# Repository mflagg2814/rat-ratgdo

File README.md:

# XIAO ESP32-C6 / ESP32-C5 board

> [!IMPORTANT]
> This board has been built and tested to work with ESP32-C6.\
> Use it at your own risk and without expectation of support.\

AI disclosure: Board layout is my own. AI was used for verification, documentation, schematic cleanup, and minor board cleanup.

[`kicad_files/XIAO ESP32C6`](kicad_files/XIAO%20ESP32C6) is a small Security+ 2.0 interface for the ESPHome `secplus_gdo` component, built around a surface-mounted Seeed XIAO ESP32-C6. Compared with the [D1 Mini - ESP32](kicad_files/D1%20Mini%20-%20ESP32) board it is based on:

- **MCU:** a XIAO ESP32-C6 replaces the D1 Mini ESP32. TX is on GPIO22 (D4) and RX on GPIO18 (D10). As before, the module is powered from its own USB port. The same footprint and pinout also accept a Seeed XIAO ESP32-C5 (see the [board README](kicad_files/XIAO%20ESP32C6/README.md#xiao-esp32-c5-compatibility) for the C5 substitutions).
- **RX:** a 10k pull-up to 3V3 is added, because the firmware does not enable an internal one.
- **Values:** the TX GPIO pulldown is 4.7k (was 10k), and the RED-to-ground bias is 100k (was 10k).
- **Protection:** a 15 V unidirectional TVS is added on the RED line.
- **Obstruction:** the black-wire sensing circuit is removed, since obstruction status is read from the serial protocol.
- **Terminal:** A single 2-pole WAGO push-button terminal replaces the 3-pole connector options. Accepts 20-24 AWG.

The folder includes a [BOM](kicad_files/XIAO%20ESP32C6/BOM.md) with DigiKey part numbers, a [schematic PDF](kicad_files/XIAO%20ESP32C6/c6gdo-schematic.pdf), and a [README](kicad_files/XIAO%20ESP32C6/README.md) with the full list of changes and the reasoning behind them. The project needs KiCad 10 and contains its own symbol, footprint and 3D-model libraries.

## XIAO ESP32-C5 compatibility
This board was designed for the XIAO ESP32-C6. The pinouts are also chosen for XIAO ESP32-C5 compatibility. I'm unsure of precedent for the GDO firmware- it may or may not function on C5.

## Firmware
Intended for use with SecPlus GDO firmware using the ESP-IDF framework.

An example ESPHome YAML would be an adaptation of `grgdov3-board-secplus-gdo-thread.yaml`, found [here](https://github.com/GelidusResearch/grgdo). Note that you will at a minimum need to remap the UART pins and change the board/variant to match.

## Case
STLs for a compact 3D printed case will be available upon validation against the final build. There will be an internal antenna variant plus C6 and C5 external antenna cutout variants.

---

# rat-ratgdo
RAGE
AGAINST
THE
RATGDO

Credit and inspiration for this work goes to [@rlowens](https://github.com/rlowens) to let me know that there are other technical folks out there who needed this other than myself.

## Overview
This is an open source schematic for the ratgdo, based on the v2.5 [ratgdo](https://github.com/PaulWieland/ratgdo) PCB and code but installed using the [ESPHome fork](ESPHome%20vs%20native%20ratgdo.md) of ratgdo.  This project was created to allow people who need a ratgdo solution for their garage door opener but either cannot, or choose not to, source the solution from Paul Wieland. It also ensures that the PCB can be recreated as and when the project maintainer gives up on the project (much like Chamberlain themselves might do with their MyQ Cloud Service) and stops selling PCBs. 

### You are expected to know how to create the described circuit using your own prototyping skills.  That is, this project is for people who can solder well and know how to read schematics

The ***basic*** PCB schematic shown here in the Readme does not describe any circuitry other than the serial line garage door control and obstruction sensor.  All other optional features provided by ratgdo can be reverse engineered as needed, or may already be solved by one of the schematics the community has uploaded!

 As of January 2023, there are now multiple sources for commercially sold ratgdo boards.  **However if you want to buy a pre-made ratgdo setup, we recommend purchasing one [from Paul Wieland](https://github.com/PaulWieland/ratgdo) so as to reward the original creator.**

_Simple basic schematic for a Wemos D1 Mini based module_

See images of a [working breadboard prototype](images/Breadboard_working.png) and the [subsequent soldered prototype using a D1 shield](images/Simple%20prototype%20using%20D1%20shield.jpg).  Both of these prototypes are using 2n7000 MOSFETs exclusively, but that is because they are prototypes and whether a 2n7000 will work for TX will depend greatly on who manufactured your 2n7000.  See the section below on needed components for context.

## Components needed for basic functionality
The basic schematic shown above assumes the use of through-hole components.  If you wish to use SMD components, please refer to the [FAQ](FAQ.md#what-if-i-want-to-use-sot-23-smd-components), and you can also check out the community-provided schematics, which include SMD-based designs.

For this basic design, aside from the obvious requirement of a [supported ESP-32 or ESP8266 board](Supported%20Boards.md) flashed with the [ESPHome version](https://github.com/ratgdo/esphome-ratgdo), you will need:
- 3x 10 kohm (kilo-ohm) resistors
- 1x 2n7000 MOSFET for the RX pin
- 1x AO3400A (soldered to a SOT23 to DIP adapter board) for the TX pin.

It is also recommended you aquire a suitable 3-post screw terminal and some red, white, and black wire for connecting to the door opener.  These connections are very low current, so you can get away with fairly thin wire.

**Note:**  You may **try** to use a 2n7000 MOSFETs for **both** RX and TX, however depending on the manufacturere of your 2n7000 and its production batch, it might not be 100% reliable for the TX circuit because the ~3v switching signal from the ESP8266 may not be enough to trigger the gate of the 2n7000.  There are many examples working using the 2n7000 however, so it might work.  If you have reliability issues for sending commands, we can only recommend you use the AO3400A SMD MOSFET, soldered to a SOT23-to-DIP adapter board.  

## INSTALL REQUIREMENTS
For both this basic schematic shown here in the Readme and how they it is laid out, you must use the ESPHome fork of ratgdo and - for ESP8266 based boards - select the "ratgdo v2.5x" image on the ESPhome [web installer page](https://ratgdo.github.io/esphome-ratgdo/).  For ESP32 based boards the above does not currently apply and you must use the v2.0 installer and follow our basic ESP-32 schematic we provide in the Supported Boards page.

For the ESP8266 based boards, if installing using Paul Wieland's native ratgdo installer and you install for a v2.0 board, you must wire your TX to D4 (GPIO2) rather than D1 (GPIO5).

## Having a PCB printed
You may use the files from the [schematics folder](kicad_files) to have your own PCB printed.  Shown is an example 3D render of an ESP32 based board using a Wemos ESP32 D1 board.

_An example of the D1 Mini ESP32 Wide Format_

Here is an example of a printed PCB with a raw ESP8266 and an LM2596 module, for being powered by a GDO with the battery backup capabilities.

_An example of a PCB using a bare ESP8266 and LM2596 module_

### Schematic options
The community has provided a few options of schematic files suitable for sending to a PCB printing company.
- [Wemos D1 Mini ESP8266](kicad_files/D1%20Mini%20-%20ESP8266)
- [Wemos D1 Mini ESP32](kicad_files/D1%20Mini%20-%20ESP32) (massive overkill for ratgdo but it's your choice!)
- [Wemos D1 Mini ESP32 Wide Format](kicad_files/D1%20Mini%20Wide%20-%20ESP32)
- [Bare ESP8266 module](kicad_files/Bare%20ESP8266)
- [Seeed XIAO ESP32-C6](kicad_files/XIAO%20ESP32C6) (untested; KiCad 10; see the note at the top)

> If you just want to try ordering a board from somewhere like PCBWay, then check out the most recent [build artifacts](https://github.com/Kaldek/rat-ratgdo/actions/workflows/pcb.yaml)

## How the ratgdo circuit works
The ratgdo circuitry which we cover in this project consists of two sections; Garage Door control and obstruction sensors.

### Garage Door Control
#### Description of the Chamberlain configuration
The Chamberlain garage door control circuit is a two-wire setup consisting of a Ground, and a combined +12v power and serial data line.  The serial data line is held at 12v unless data transmission is occurring.  Data transmission is performed by pulling the 12v line down to GND for each data bit.  The benefit here is that a single wire can be used for providing power to door control panels and data transmssion on a single wire.  The use of appropriately sized capacitors in door control panels means they do not switch off during data transmission.

#### How ratgdo interfaces with the Chamberlain wiring
The ratgdo taps into the red control wire and uses this single wire for transmission of commands onto the serial bus, and for receiving data from the serial bus.  As it is a single wire protocol and operates half-duplex, the ratgdo circuitry uses N-channel MOSFETs wired in a manner which allows the ESP8266 to never transmit when the serial line is already low.

In operation, this means that the ratgdo is mostly listening to the serial bus to ensure it is keeping track of the state of the door.  For example, if the door is manually opened (or opened by use of the MyQ app even), these events are broadcast onto the serial bus by the door controller.  ratgdo is therefore able to know that the state of the door has changed.  In turn, this means that when controlling ratgdo via Home Assistant, the status of the door in HA is always up to date.

#### Wiring to Garage Door

### Obstruction sensor
The ratgdo monitors the real-time state of the obstruction sensors directly.  We assume this is because obstruction status is not broadcast in real time by the door controller, and safety is paramount.  It allows you to set up real-time alerts in Home Assistant for any time the door is obstructed.  The ratgdo taps into the obstruction sensor power wire which also acts as a communication bus, however the signalling is only an ongoing status of whether the obstruction sensors are working and whether there is an obstruction.

## Contributing
This is a fully open repo, in that we welcome any and all additions for all sorts of Edge Cases.  If you come up with something and would like it to be available to the community, raise a Pull Request and we'll work with you to get it published!

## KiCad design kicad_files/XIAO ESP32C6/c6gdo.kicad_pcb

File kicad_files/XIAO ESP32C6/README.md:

# Seeed XIAO ESP32-C6 / ESP32-C5 KiCad files

> [!IMPORTANT]
> This board has been built and tested to work with ESP32-C6.\
> Use it at your own risk and without expectation of support.\
> My opener also required a patched gdolib to address a buffer overrun while opening/closing. See Firmware below.

A small (28.4 × 21.05 mm, 2-layer) Security+ 2.0 interface based on this repository's D1 Mini - ESP32 board, built around a surface-mounted [Seeed Studio XIAO ESP32-C6](https://wiki.seeedstudio.com/xiao_esp32c6_getting_started/). It connects to only the RED and WHITE wall-control wires, and the XIAO is powered from its own USB-C port.

- Schematic: [c6gdo-schematic.pdf](c6gdo-schematic.pdf) (source: `c6gdo.kicad_sch`)
- Bill of materials: [BOM.md](BOM.md) / [BOM.csv](BOM.csv)

## Case

Case STLs are in the `case` dir. Print one `bottom.stl` and one `top` per your external antenna cutout requirements. Designed for 0.2mm layer height and successfully printed in Prusament Galaxy Purple PLA.

## Firmware

The board was designed for the ESPHome [`secplus_gdo`](https://github.com/gelidusresearch/esphome-secplus-gdo) component. That component inverts the UART, which matches the two inverting MOSFET stages on this board.

Obstruction status comes from the Security+ 2.0 serial protocol, so no obstruction pin is configured.

An example ESPHome YAML would be an adaptation of `grgdov3-board-secplus-gdo-thread.yaml`, found [here](https://github.com/GelidusResearch/grgdo). Note that you will at a minimum need to remap the UART pins and change the board/variant to match.

```yaml
substitutions:
  uart_tx_pin: GPIO22 # D4
  uart_rx_pin: GPIO18 # D10

esp32:
  board: seeed_xiao_esp32c6
  flash_size: 4MB
  variant: esp32c6
  framework:
    type: esp-idf
```

### gdolib patch

My opener also required the patch in `gdolib-patch` against `GelidusResearch/gdolib` v1.2.9 (5936cab). It's provided in the event your opener behaves like mine and spams messages before gdolib can service them. I don't recommend bothering with it unless you have issues stopping your opener mid-travel or issues with opening/closing state reports. Open/close, light status, etc worked fine without the patch.

## XIAO ESP32-C5 compatibility

This board was designed for the XIAO ESP32-C6. The pinouts are also chosen for XIAO ESP32-C5 compatibility. I'm unsure of precedent for the GDO firmware- it may or may not function on C5.

If you populate a C5 instead of a C6, use this in place of the substitutions/esp32 block above:

```yaml
substitutions:
  uart_tx_pin: GPIO23 # D4
  uart_rx_pin: GPIO10 # D10

esp32:
  board: seeed_xiao_esp32c5
  flash_size: 8MB
  variant: esp32c5
  framework:
    type: esp-idf
```

## Changes from the D1 Mini - ESP32 board

The starting point is [`kicad_files/D1 Mini - ESP32`](../D1%20Mini%20-%20ESP32). The core of that design is kept as is:
- Q1 (2N7002) with a 10k series resistor into its gate for RX.
- Q2 (AO3400A) with a 1k gate resistor for TX.
- A pulldown on the TX GPIO.
- A bias resistor from RED to ground.
- No power circuitry on the board (the module is powered over its own USB).

The changes are:

| | D1 Mini - ESP32 | This board | Notes |
|-|-|-|-|
| MCU | Wemos D1 Mini ESP32: TX IO22 (D1), RX IO21 (D2) | Seeed XIAO ESP32-C6: TX GPIO22 (D4), RX GPIO18 (D10) | Smaller module with WiFi 6 / Thread. Neither pin is a C6 strapping pin, and neither conflicts with the console UART, USB-JTAG or the antenna switch. D4/D10 were chosen (instead of D3/D10) so the same board also works with a XIAO ESP32-C5 — see [XIAO ESP32-C5 compatibility](#xiao-esp32-c5-compatibility). |
| RX pull-up | None | **R5** 10k to 3V3 (new) | gdolib never enables an internal pull-up on the RX pin, so without R5 the pin floats when Q1 is off. |
| TX GPIO pulldown | 10k | **R1** 4.7k | Keeps Q2 off while the ESP32 is in reset. In reset the pin's ~45 kΩ internal pull-up is enabled, which with the old 10k pulldown would set Q2's gate to about 3.3 V × 10k / 55k ≈ 0.60 V. That is just under the AO3400A's minimum turn-on threshold of 0.65 V (0.65–1.45 V). With 4.7k the gate sits at about 0.31 V. |
| RED bias to ground | 10k | **R4** 100k | Lighter load on the opener's line: about 0.13 mA instead of 1.3 mA at 12.7 V. |
| Transient protection | None | **D1** PTVS15VS1UR 15 V, 400 W unidirectional TVS (new) | Clamps transients on the wire run to the opener. |
| Obstruction | IO23 through a 10k series resistor and 10k pulldown | Removed | Obstruction status is read from the Security+ 2.0 serial protocol. |
| Connector | Three 3-pole footprint options (5.00 mm screw terminal, 3.5 mm Phoenix MCV, 2.54 mm header) | One 2-pole WAGO 250-1402 push-button terminal | Only RED and WHITE are needed. Accepts 20-24 AWG *solid* wire. |

## Wiring and mounting

- **J1 RED** → opener's red wall-control terminal. **J1 WHITE** → opener's white terminal (ground). The labels are on the back silkscreen.
- Power the XIAO from any USB-C supply.
- Mount it with a #6-32 nylon screw through the 4.0 mm hole into a SnapSkru SPM Mini drywall anchor (see the BOM).
  - A smaller diameter screw might work better. I installed the SnapScrew, ran an included metal screw through it, then installed with the nylon screw snipped to ~1-1.5cm length. Any longer and it would bind.
  - M3.5 should also work for the mounting screw.
  - I strongly recommend against a metallic screw in this position. It may interfere with the antenna.

## PCB notes

- The XIAO sits on the top side, flush with the bottom board edge. All other parts are on the back.
- The XIAO's underside pads (24–33) are **not soldered**. The footprint has no copper for them; instead it marks each one with an F.Fab outline and a rule area, so DRC flags any via placed there. The top-layer ground fill also stays out of these areas, so a flaw in the solder mask can't short a signal or power pad to ground. These pads are also left off the schematic symbol.
- Both copper layers are ground-filled, and both fills stop at y = 55 mm, leaving the board under the XIAO's antenna end free of copper.
- Stitching vias tie the two ground fills together. Most sit on a regular 3.2 mm grid, including a row along the fill edge nearest the antenna, with a few extra vias between the parts in the center. The spacing comes from the WiFi wavelength:
  - A 2.4 GHz signal has a wavelength (λ) of about 125 mm in air, or roughly 60–70 mm in FR4.
  - A common rule of thumb keeps stitching vias no more than λ/20–λ/10 apart, about 3–6 mm. That way no patch of copper is large enough to act as a resonator or slot antenna at WiFi frequencies.
  - On this board, no point where both layers are filled is more than about 3.2 mm from a stitching via.
- Under the XIAO's two rows of edge pads, only the bottom layer is ground-filled, since the top layer holds the pads. These bottom-only strips are about 4 mm wide. Each one is joined to the rest of the bottom fill along its full length, and a column of vias runs along its inner edge. So each strip is part of the ground plane rather than a separate flap, and it is far too small to resonate at 2.4 GHz (a quarter wavelength is about 15–17 mm in FR4).

## Project layout

Everything the project uses is inside this folder. Symbols, footprints and 3D models are referenced through `${KIPRJMOD}` via the project's own `sym-lib-table` and `fp-lib-table`, so the folder can be moved or renamed and opened on another machine without extra library setup.

```
c6gdo.kicad_pro / .kicad_sch / .kicad_pcb   KiCad 10 project
c6gdo-schematic.pdf                          schematic export
BOM.md, BOM.csv                              bill of materials
gerbers/                                     Gerber + Excellon drill files
c6gdo-gerbers.zip                            the same files, zipped for upload to a PCB fab
lib/c6gdo.kicad_sym                          project symbol library
lib/c6gdo.pretty/                            project footprint library
lib/c6gdo.3dshapes/                          3D models (STEP/IGES)
images/                                      3D renders
```

The files require **KiCad 10**. The Gerbers match the current board. After any board change, re-export them: copper, mask, paste, silkscreen and Edge.Cuts layers, plus separate PTH/NPTH Excellon drill files.

Sources:
- **XIAO symbol and footprint:** derived from Seeed Studio's official XIAO KiCad library.
- **XIAO 3D model** (`lib/c6gdo.3dshapes/seeed-studio-xiao-esp32c6-v2.step`): "[3D model for Seeed Studio XIAO ESP32C6](https://www.printables.com/model/1338408-3d-model-for-seeed-studio-xiao-esp32c6)" from Printables. It is licensed under [CC BY-SA 4.0](https://creativecommons.org/licenses/by-sa/4.0/) and included unmodified.
- **WAGO footprint and 3D model:** from the [250-1402 Ultra Librarian CAD download on DigiKey](https://www.digikey.com/en/models/15551338?tab=ultralibrarian).
- **Everything else:** the remaining footprints and 3D models come from the standard KiCad libraries.

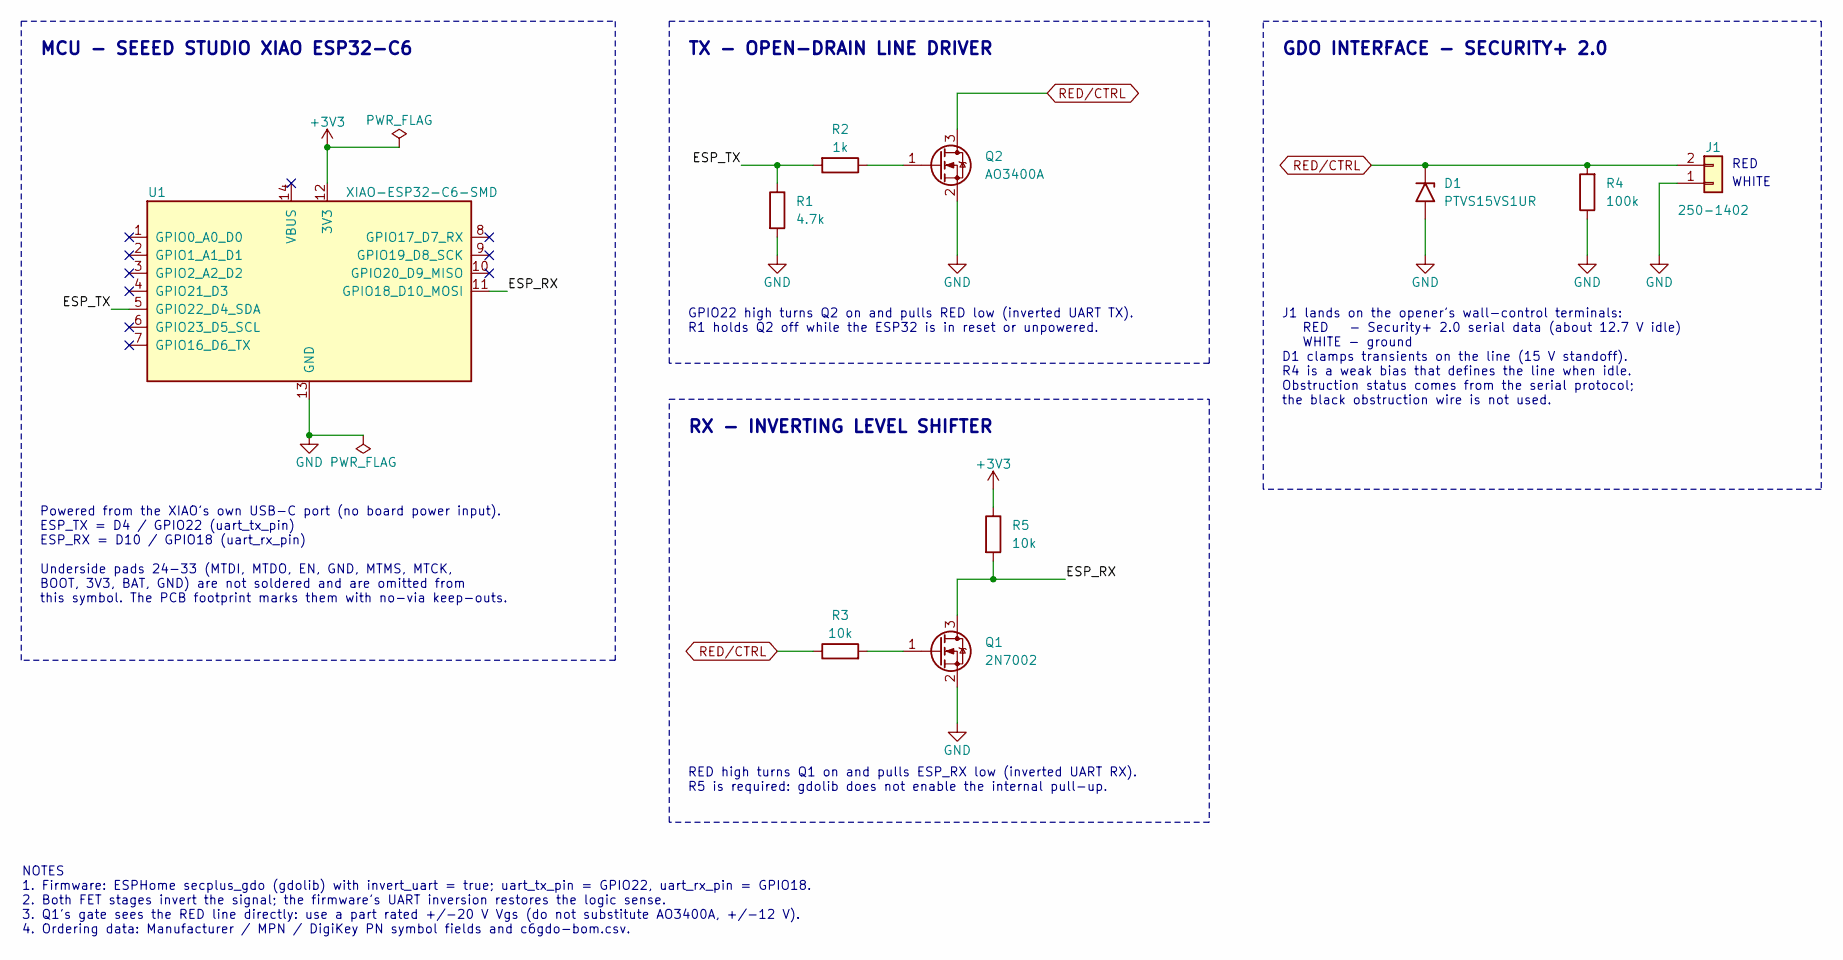
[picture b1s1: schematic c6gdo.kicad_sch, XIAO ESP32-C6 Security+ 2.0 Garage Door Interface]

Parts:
D1: PTVS15VS1UR; Nexperia_CFP3_SOD-123W; MPN PTVS15VS1UR,115; DigiKey PN 1727-5315-1-ND
J1: 250-1402; CONN2_250-1402_WAG; MPN 250-1402; DigiKey PN 2946-250-1402-ND
Q1: 2N7002; SOT-23_Handsoldering; MPN 2N7002; DigiKey PN 2N7002NCT-ND
Q2: AO3400A; SOT-23_Handsoldering; MPN AO3400A; DigiKey PN 785-1000-1-ND
R1: 4.7k; R_0805_2012Metric_Pad1.20x1.40mm_HandSolder; MPN ERA-6AEB472V; DigiKey PN P4.7KDACT-ND
R2: 1k; R_0805_2012Metric_Pad1.20x1.40mm_HandSolder; MPN ERA-6AEB102V; DigiKey PN P1.0KDACT-ND
R3, R5: 10k; R_0805_2012Metric_Pad1.20x1.40mm_HandSolder; MPN ERA-6AED103V; DigiKey PN P123794CT-ND
R4: 100k; R_0805_2012Metric_Pad1.20x1.40mm_HandSolder; MPN ERA-6AEB104V; DigiKey PN P100KDACT-ND
U1: XIAO-ESP32-C6-SMD; MPN 113991254; DigiKey PN 1597-113991254-ND

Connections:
+3V3: R5.1, U1.12 (3V3)
/ESP_RX: Q1.3 (D), R5.2, U1.11 (GPIO18_D10_MOSI)
/ESP_TX: R1.1, R2.2, U1.5 (GPIO22_D4_SDA)
GND: D1.2 (A), J1.1, Q1.2 (S), Q2.2 (S), R1.2, R4.1, U1.13 (GND)
unnamed: Q1.1 (G), R3.2
unnamed: Q2.1 (G), R2.1
RED/CTRL: D1.1 (K), J1.2, Q2.3 (D), R3.1, R4.2

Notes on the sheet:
GPIO22 high turns Q2 on and pulls RED low (inverted UART TX). R1 holds Q2 off while the ESP32 is in reset or unpowered.
J1 lands on the opener's wall-control terminals: RED - Security+ 2.0 serial data (about 12.7 V idle) WHITE - ground D1 clamps transients on the line (15 V standoff). R4 is a weak bias that defines the line when idle. Obstruction status comes from the serial protocol; the black obstruction wire is n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
NOTES 1. Firmware: ESPHome secplus_gdo (gdolib) with invert_uart = true; uart_tx_pin = GPIO22, uart_rx_pin = GPIO18. 2. Both FET stages invert the signal; the firmware's UART inversion restores the logic sense. 3. Q1's gate sees the RED line directly: use a part rated +/-20 V Vgs (do not substitute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
RX - INVERTING LEVEL SHIFTER
RED high turns Q1 on and pulls ESP_RX low (inverted UART RX). R5 is required: gdolib does not enable the internal pull-up.
WHITE
RED
MCU - SEEED STUDIO XIAO ESP32-C6
GDO INTERFACE - SECURITY+ 2.0
TX - OPEN-DRAIN LINE DRIVER
Powered from the XIAO's own USB-C port (no board power input). ESP_TX = D4 / GPIO22 (uart_tx_pin) ESP_RX = D10 / GPIO18 (uart_rx_pin) Underside pads 24-33 (MTDI, MTDO, EN, GND, MTMS, MTCK, BOOT, 3V3, BAT, GND) are not soldered and are omitted from this symbol. The PCB footprint marks them with no-v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

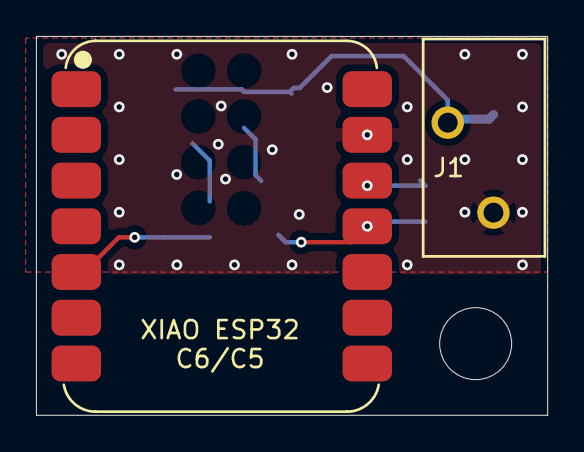
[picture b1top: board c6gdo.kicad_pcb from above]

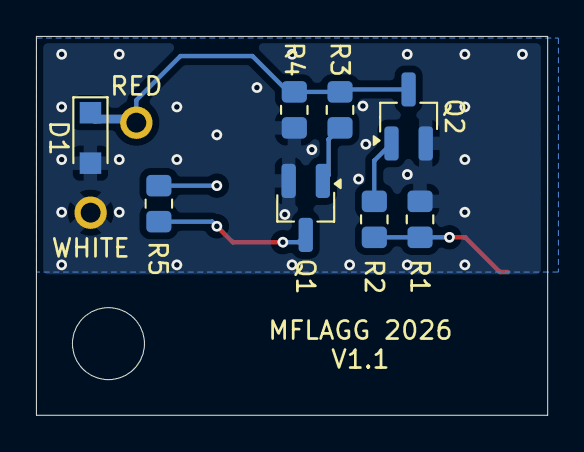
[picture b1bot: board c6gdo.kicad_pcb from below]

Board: 2 copper layers, 28.4 x 21.0 mm, 11 parts (8 on the bottom side), 7 nets.

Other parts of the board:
H1: MountingHole_4mm

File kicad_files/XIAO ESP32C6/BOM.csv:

Item,Reference,Qty,Value,Description,Package,Manufacturer,MPN,DigiKey PN,Notes
1,U1,1,XIAO ESP32C6,ESP32-C6 WiFi6/BLE5/802.15.4 module,XIAO 14-pad castellated,"Seeed Technology Co., Ltd",113991254,1597-113991254-ND,Standard (non-pre-soldered) version; solder by castellated edges
2,J1,1,250-1402,"PCB terminal block, push-button, 2-pole (RED + WHITE from GDO)",THT 2.54 mm pitch,WAGO Corporation,250-1402,2946-250-1402-ND,
3,D1,1,PTVS15VS1UR,"TVS diode, unidirectional, 15 V standoff, 400 W",SOD-123W,Nexperia,"PTVS15VS1UR,115",1727-5315-1-ND,Cathode to RED/CTRL
4,Q1,1,2N7002,"N-ch MOSFET 60 V, RX level shifter",SOT-23,onsemi,2N7002,2N7002NCT-ND,Needs +/-20 V gate rating - do not substitute AO3400A
5,Q2,1,AO3400A,"N-ch MOSFET 30 V, open-drain TX driver",SOT-23,Alpha & Omega Semiconductor Inc.,AO3400A,785-1000-1-ND,
6,R1,1,4.7k,"Resistor 4.7 kOhm 0.1% 1/8 W, TX gate pulldown",0805,Panasonic Industry,ERA-6AEB472V,P4.7KDACT-ND,
7,R2,1,1k,"Resistor 1 kOhm 0.1% 1/8 W, Q2 gate series",0805,Panasonic Industry,ERA-6AEB102V,P1.0KDACT-ND,
8,"R3, R5",2,10k,"Resistor 10 kOhm 0.5% 1/8 W, Q1 gate series / RX pull-up",0805,Panasonic Industry,ERA-6AED103V,P123794CT-ND,
9,R4,1,100k,"Resistor 100 kOhm 0.1% 1/8 W, RED/CTRL bias",0805,Panasonic Industry,ERA-6AEB104V,P100KDACT-ND,
10,H1,1,#6-32 x 1 in,"Machine screw, pan head Phillips, nylon",Head 6.68 mm dia,Essentra Components,010632PW100,RPC7858-ND,Mechanical - not in schematic
11,-,1,SnapSkru SPM Mini,"Self-drilling drywall anchor, 3/8-5/8 in drywall, #6-#8 screws",Glass-filled nylon,TOGGLER (Mechanical Plastics),SnapSkru SPM Mini,,Not stocked by DigiKey
12,PCB,1,c6gdo,"Bare PCB, 28.4 x 21.05 mm",2-layer 1.6 mm FR4,,,,
